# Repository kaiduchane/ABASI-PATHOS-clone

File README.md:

# ABASI-PATHOS-clone
The Abasi Pathos is a modern high-gain distortion pedal designed by guitarist Tosin Abasi and Horizon Devices. This project is an open-source clone that reverse-engineers the circuit for educational purposes and DIY builders.
This pedal features a three-band active EQ, dual-stage clipping circuit, and tight low-end response designed for modern progressive metal tones. The design uses through-hole components where possible to make it accessible for beginners while maintaining the sonic characteristics of the original.
Key Features:

Adjustable gain structure with asymmetrical clipping
Active 3-band EQ (Bass/Mid/Treble)
High input impedance JFET buffer
True bypass switching
Standard 9V center-negative power

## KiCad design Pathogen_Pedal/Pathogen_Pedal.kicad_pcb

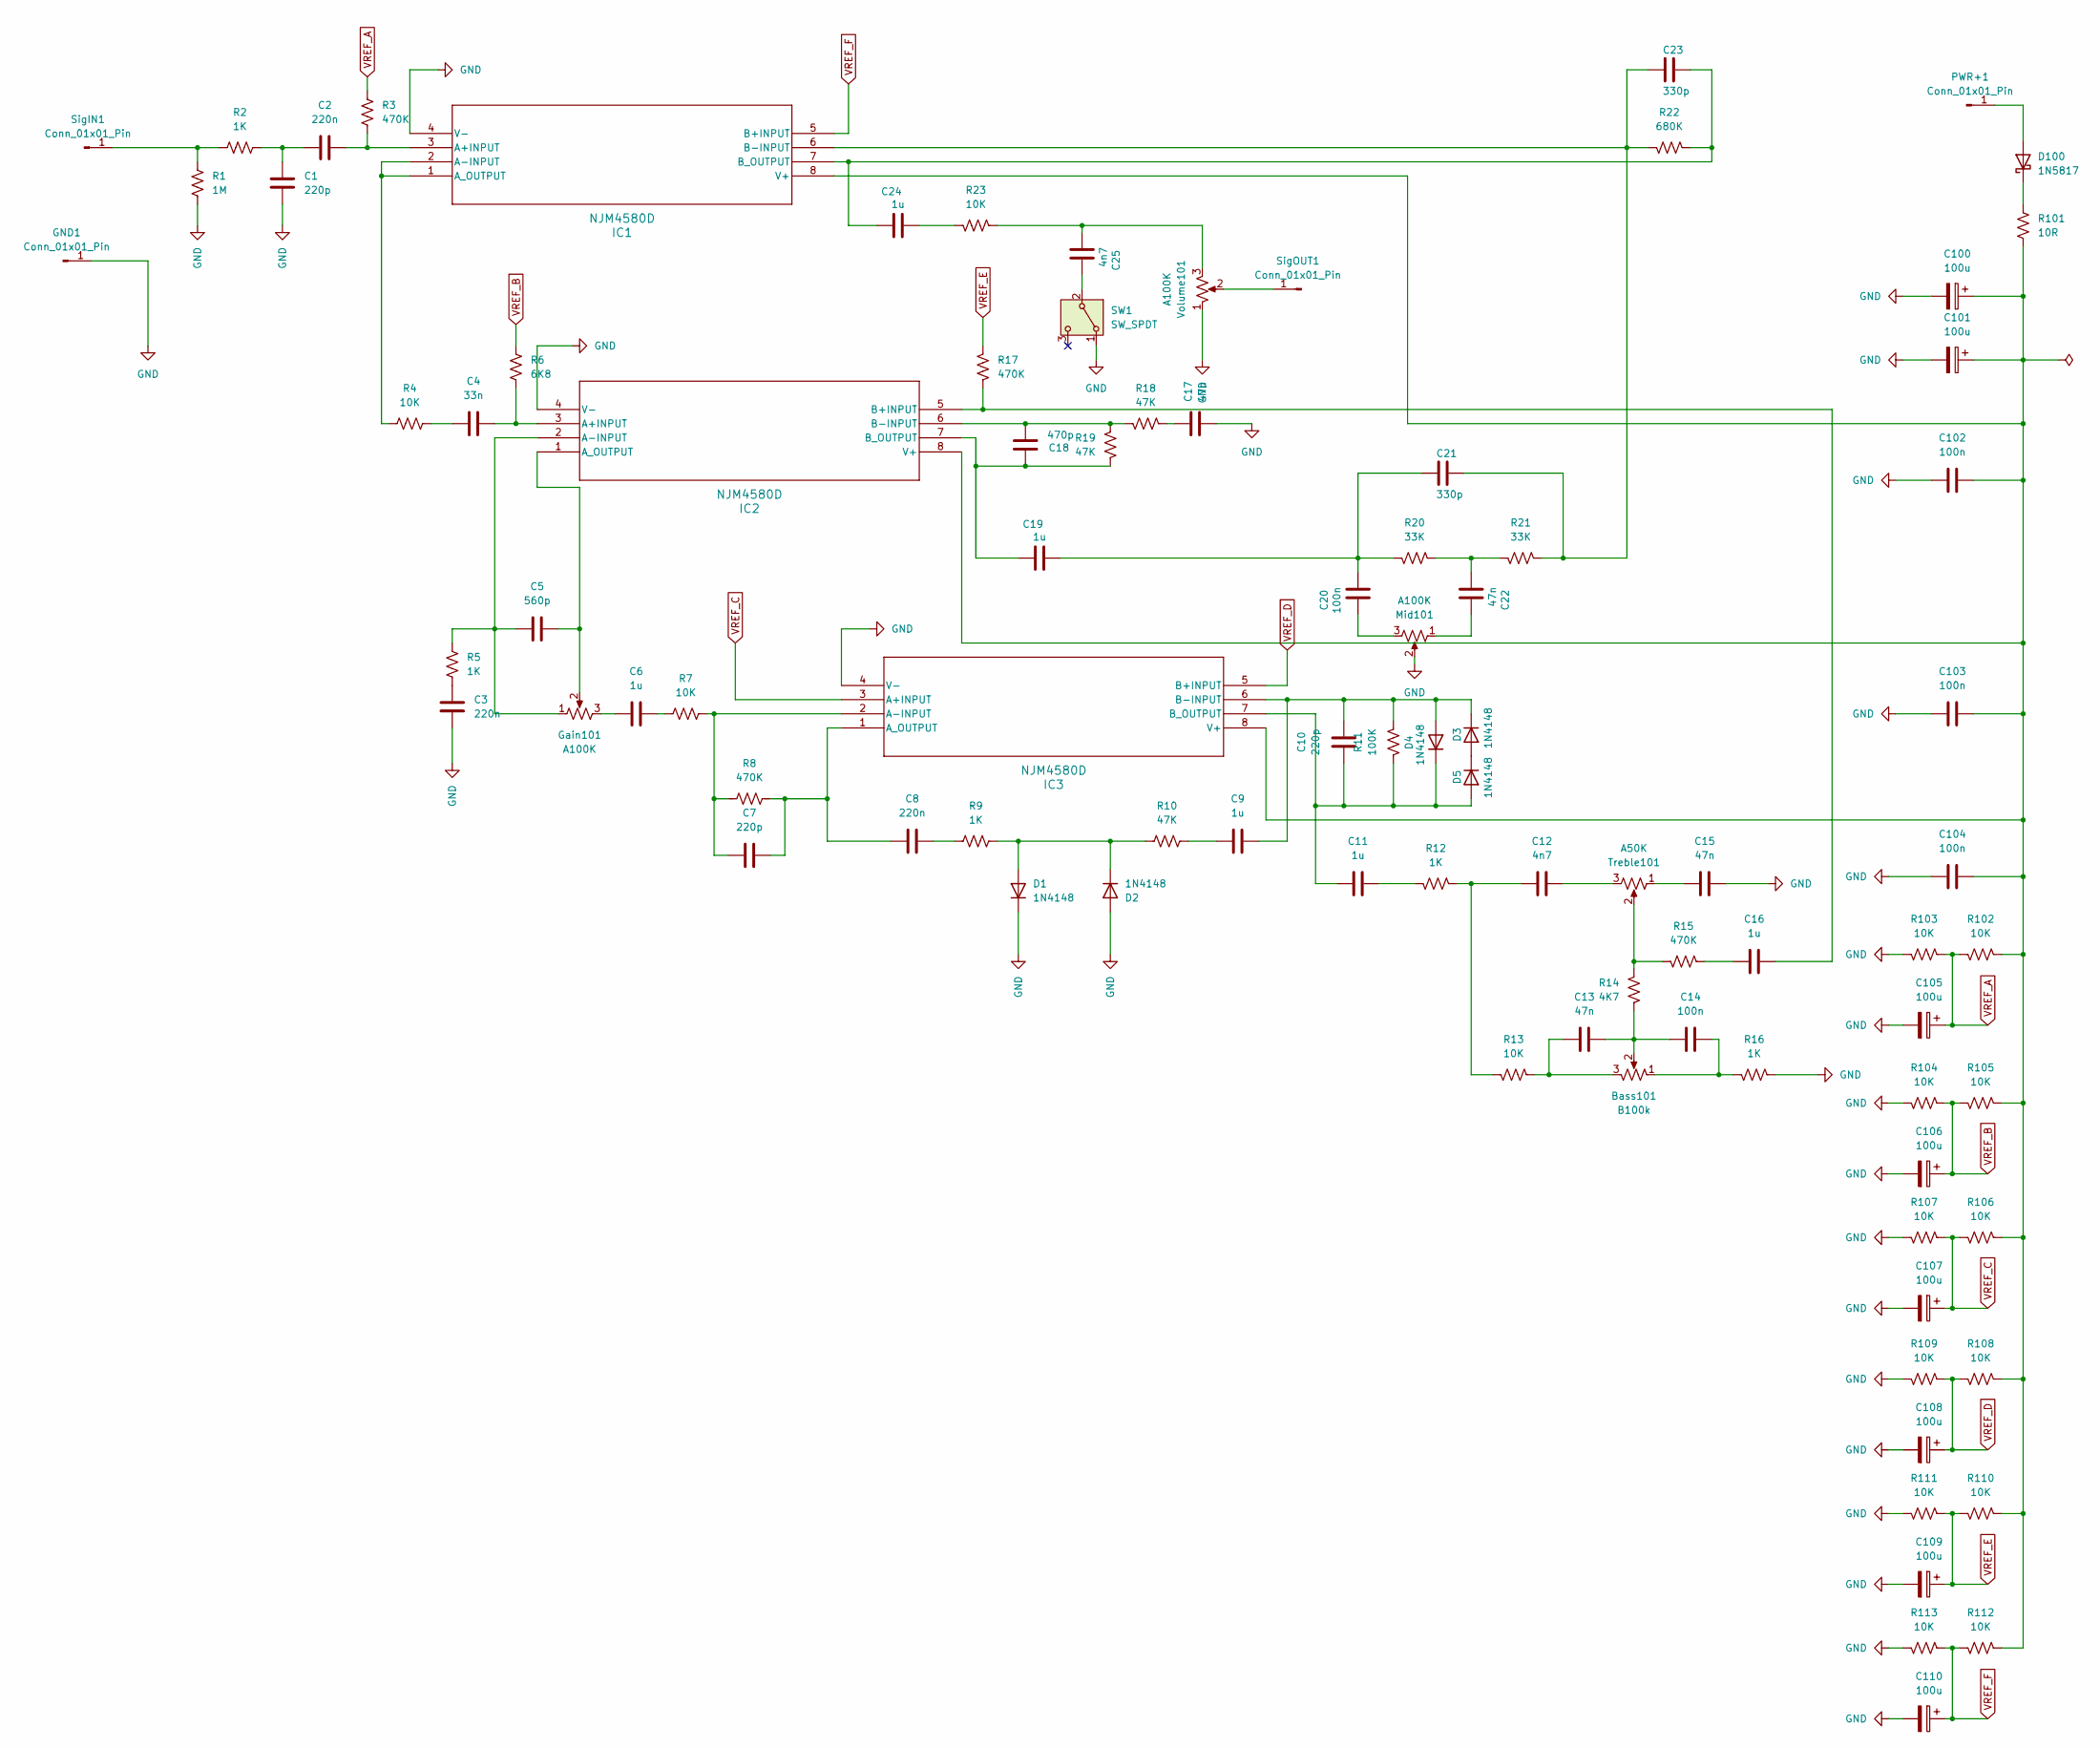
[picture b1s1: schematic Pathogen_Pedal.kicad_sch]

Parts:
Bass101: B100k; 16MM_PADS.2
C1, C7, C10: 220p; 5mm_10p-180n
C2, C3, C8: 220n; 5mm_1n-300n
C4: 33n; 7.62mm
C5: 560p; 7.62mm
C6, C9, C11, C16, C19, C24: 1u; C_Axial_L12.0mm_D6.5mm_P15.00mm_Horizontal
C12, C25: 4n7; 5mm_1n-300n
C13, C15, C17, C22: 47n; C_Axial_L17.0mm_D6.5mm_P20.00mm_Horizontal
C14, C20, C102, C103, C104: 100n; 5mm_1n-300n
C18: 470p; 5mm_10p-180n
C21, C23: 330p; 7.62mm
C100, C101, C105, C106, C107, C108, C109, C110: 100u; 0503
D1, D2, D3, D4, D5: 1N4148; DO41-2
D100: 1N5817; DO35-3
GND1: Conn_01x01_Pin; PAD3
Gain101: A100K; 16MM_PADS.2
IC1, IC2, IC3: NJM4580D; DIP08
Mid101: A100K; 16MM_PADS.2
PWR+1: Conn_01x01_Pin; PAD3
R1: 1M; 0.3%22.B
R2, R5, R9, R12, R16: 1K; 0.3%22.B
R3, R8, R15, R17: 470K; 0.3%22.B
R4, R7, R13, R23, R102, R103, R104, R105, R106, R107, R108, R109, R110, R111, R112, R113: 10K; 0.5%22
R6: 6K8; 0.3%22.B
R10, R18, R19: 47K; 0.3%22.B
R11: 100K; 0.2%22
R14: 4K7; 0.3%22.B
R20, R21: 33K; 0.4%22
R22: 680K; 0.3%22.B
R101: 10R; 0.3%22.B
SW1: SW_SPDT; SPDT.WIRE
SigIN1: Conn_01x01_Pin; PAD3
SigOUT1: Conn_01x01_Pin; PAD3
Treble101: A50K; 16MM_PADS.2
Volume101: A100K; 16MM_PADS.2

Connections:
GND: C1.2, C3.1, C15.2, C17.1, C100.2, C101.2, C102.1, C103.1, C104.1, C105.2, C106.2, C107.2, C108.2, C109.2, C110.2, D1.1 (K), D2.2 (A), GND1.1, IC1.4 (V-), IC2.4 (V-), IC3.4 (V-), Mid101.2, R1.1, R16.2, R103.1, R104.1, R107.1, R109.1, R111.1, R113.1, SW1.1 (A), Volume101.1
unnamed: Bass101.1, C14.2, R16.1
unnamed: Bass101.2, C13.2, C14.1, R14.1
unnamed: Bass101.3, C13.1, R13.2
unnamed: C1.1, C2.1, R2.1
unnamed: C3.2, R5.1
unnamed: C4.1, R4.2
unnamed: C6.1, R7.2
unnamed: C6.2, Gain101.3
unnamed: C8.1, R9.2
unnamed: C9.2, R10.1
unnamed: C11.2, R12.1
unnamed: C12.1, R12.2, R13.1
unnamed: C12.2, Treble101.3
unnamed: C15.1, Treble101.1
unnamed: C16.1, R15.1
unnamed: C17.2, R18.2
unnamed: C19.1, C20.1, C21.1, R20.1
unnamed: C20.2, Mid101.3
unnamed: C22.1, R20.2, R21.1
unnamed: C22.2, Mid101.1
unnamed: C24.1, R23.1
unnamed: C25.1, R23.2, Volume101.3
unnamed: D1.2 (A), D2.1 (K), R9.1, R10.2
unnamed: D3.2 (A), D5.1 (K)
unnamed: C9.1, C10.1, D3.1 (K), D4.2 (A), IC3.6 (B-INPUT), R11.1
unnamed: C10.2, C11.1, D4.1 (K), D5.2 (A), IC3.7 (B_OUTPUT), R11.2
unnamed 27: D100.2 (A), PWR+1.1; also elsewhere on the board
unnamed 28: D100.1 (K), R101.2; also elsewhere on the board
unnamed: C2.2, IC1.3 (A+INPUT), R3.2
unnamed: IC1.1 (A_OUTPUT), IC1.2 (A-INPUT), R4.1
unnamed: C21.2, C23.1, IC1.6 (B-INPUT), R21.2, R22.1
unnamed: C23.2, C24.2, IC1.7 (B_OUTPUT), R22.2
unnamed: C100.1, C101.1, C102.2, C103.2, C104.2, IC1.8 (V+), IC2.8 (V+), IC3.8 (V+), R101.1, R102.2, R105.2, R106.2, R108.2, R110.2, R112.2
unnamed: C4.2, IC2.3 (A+INPUT), R6.1
unnamed: C5.2, Gain101.1, IC2.2 (A-INPUT), R5.2
unnamed: C5.1, Gain101.2, IC2.1 (A_OUTPUT)
unnamed: C16.2, IC2.5 (B+INPUT), R17.2
unnamed: C18.2, IC2.6 (B-INPUT), R18.1, R19.2
unnamed: C18.1, C19.2, IC2.7 (B_OUTPUT), R19.1
unnamed: C7.2, IC3.2 (A-INPUT), R7.1, R8.2
unnamed: C7.1, C8.2, IC3.1 (A_OUTPUT), R8.1
unnamed: R14.2, R15.2, Treble101.2
unnamed: C25.2, SW1.2 (B)
unnamed: R1.2, R2.2, SigIN1.1
unnamed: SigOUT1.1, Volume101.2
VREF_A: C105.1, R3.1, R102.1, R103.2
VREF_B: C106.1, R6.2, R104.2, R105.1
VREF_C: C107.1, IC3.3 (A+INPUT), R106.1, R107.2
VREF_D: C108.1, IC3.5 (B+INPUT), R108.1, R109.2
VREF_E: C109.1, R17.1, R110.1, R111.2
VREF_F: C110.1, IC1.5 (B+INPUT), R112.1, R113.2

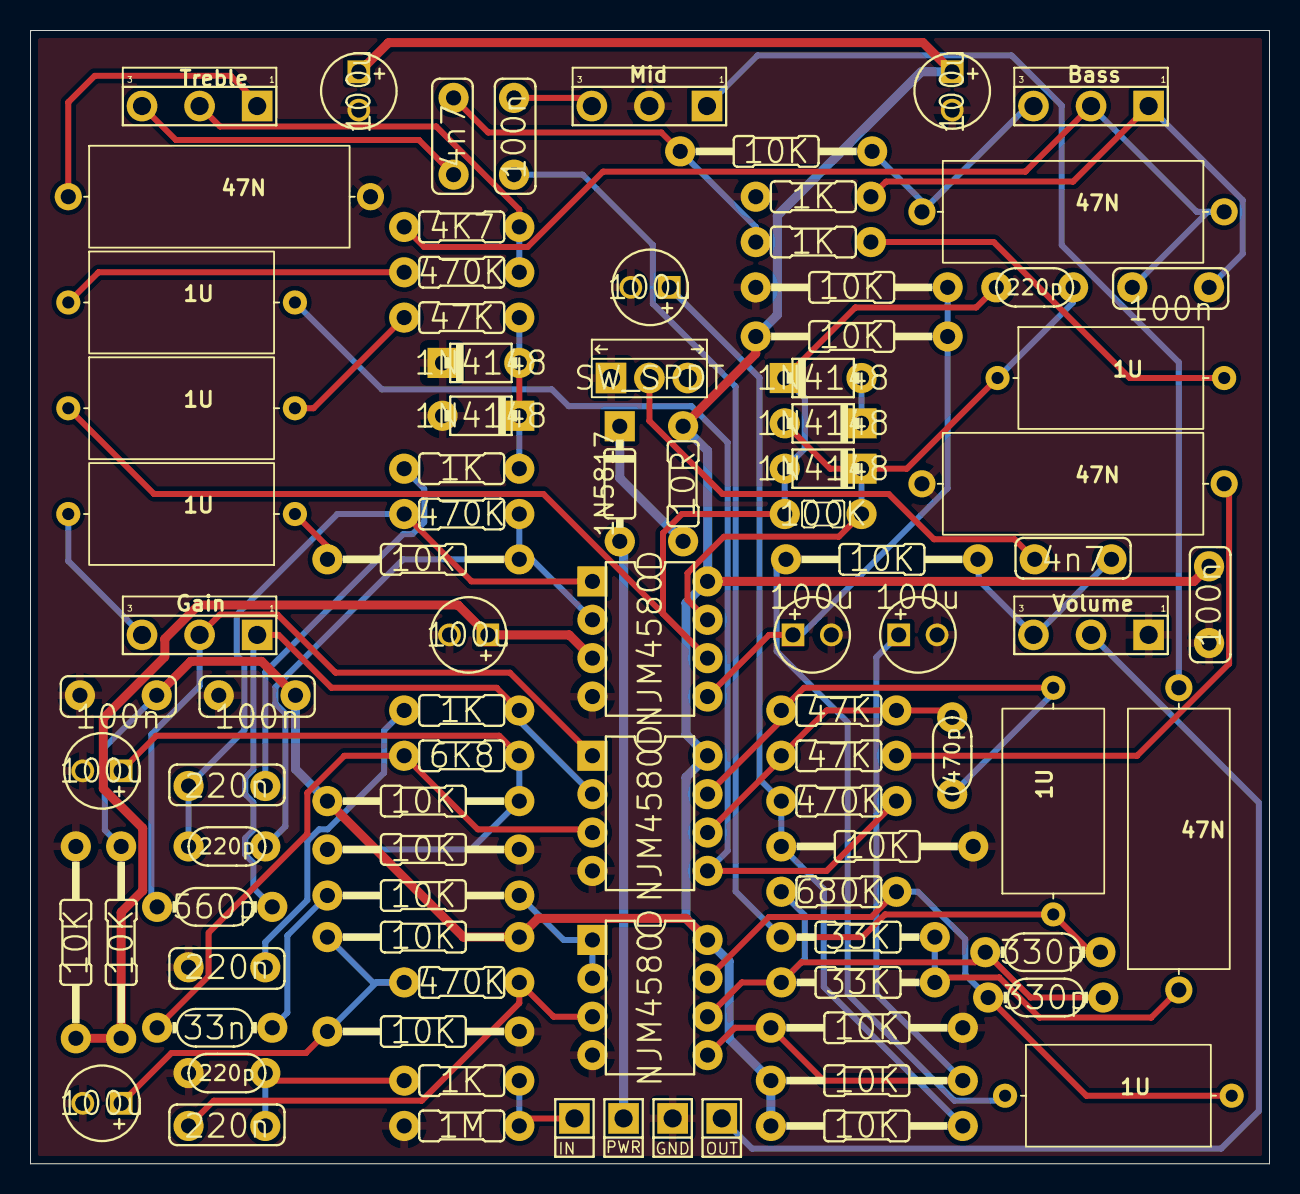
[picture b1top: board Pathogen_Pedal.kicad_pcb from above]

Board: 4 copper layers, 82.0 x 75.0 mm, 91 parts (0 on the bottom side), 52 nets.

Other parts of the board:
1N5817: 1N5817; DO35-3

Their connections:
unnamed 27: 1N5817.2 (A); also elsewhere on the board
unnamed 28: 1N5817.1 (K); also elsewhere on the board

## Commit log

2026-02-05 Pathos Folder
2026-02-05 Gerber files for JLC PCB
